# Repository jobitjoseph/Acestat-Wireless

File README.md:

# Acestat-Wireless
Acestat Wireless

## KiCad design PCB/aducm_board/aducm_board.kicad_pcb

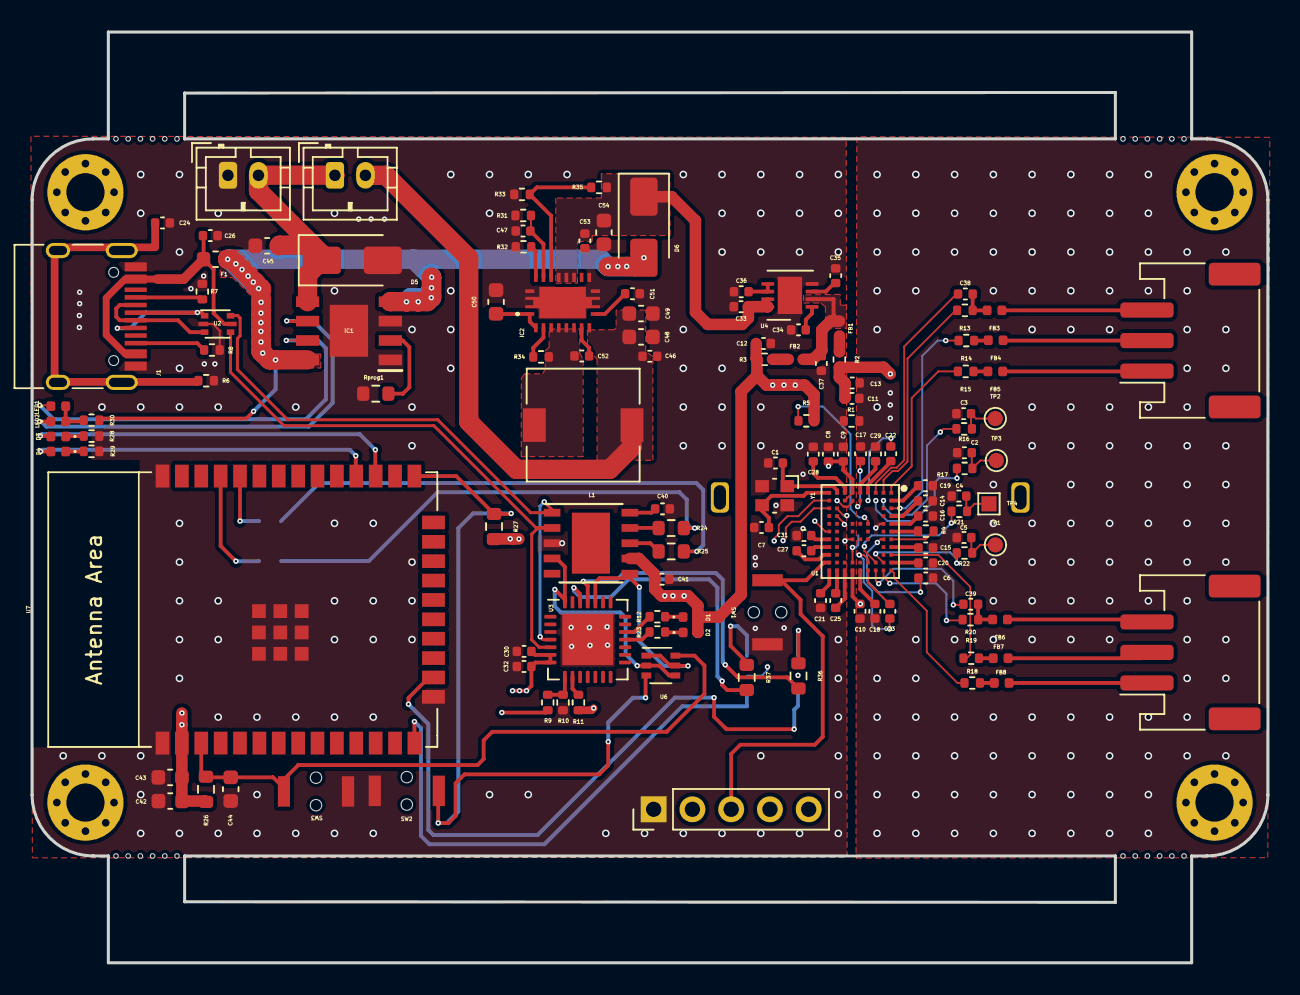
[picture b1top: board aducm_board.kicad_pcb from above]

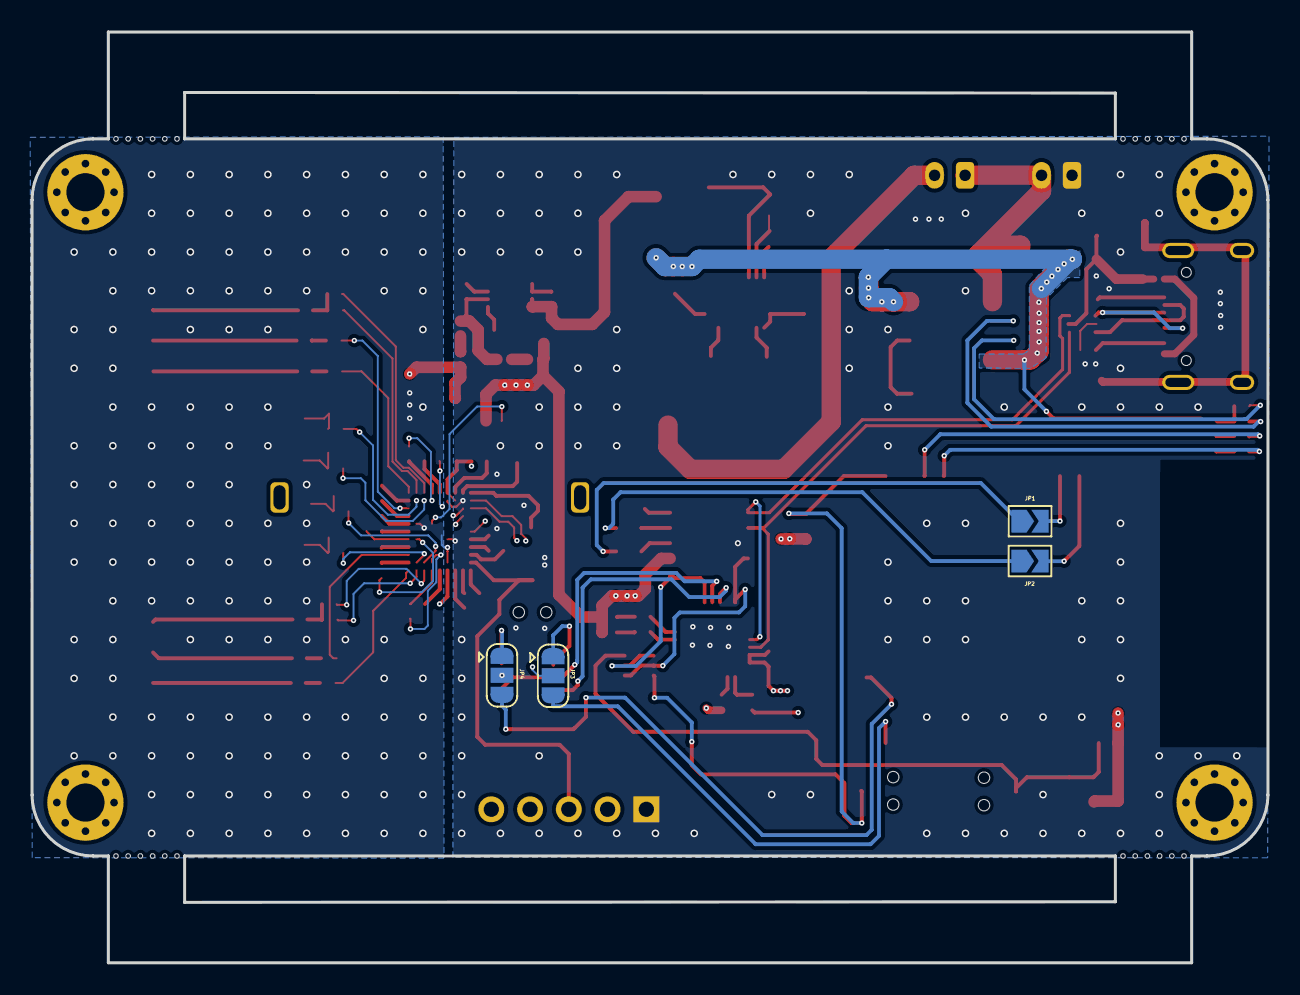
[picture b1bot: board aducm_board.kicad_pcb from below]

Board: 4 copper layers, 81.0 x 61.0 mm, 142 parts (4 on the bottom side), 117 nets.

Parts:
C1, C7: 7pF; C_0402_1005Metric
C2, C3, C4, C5, C8, C9, C10, C11, C12, C19, C20, C22, C25, C26, C27, C32, C38, C39: 0.1uF; C_0402_1005Metric
C6: 220pF; C_0402_1005Metric
C13, C30, C33, C34, C37: 10uF; C_0402_1005Metric
C14, C15, C16, C23: 4.7uF; C_0402_1005Metric
C17, C18, C21, C28, C29, C31: 0.47uF; C_0402_1005Metric
C24: 4.7nF; C_0402_1005Metric
C35, C36: 1uF; C_0402_1005Metric
C40, C46, C52, C53: 0.1uf; C_0402_1005Metric
C41: 0.1UF; C_0402_1005Metric
C42, C48, C49: 10uf; C_0603_1608Metric
C43: 1uf; C_0603_1608Metric
C44: 0.1uf; C_0603_1608Metric
C45: 10uF; C_0603_1608Metric
C47: 470pf; C_0402_1005Metric
C50: 2.2uf; C_0603_1608Metric
C51: 8.2nf; C_0402_1005Metric
C54: 100uf; C_0603_1608Metric
D1, D3, D4: TX; LED_0402_1005Metric
D2: RX; LED_0402_1005Metric
D5, D6: 1N4007; D_SMA
F1: 0.5A; Fuse_0603_1608Metric
FB1, FB2, FB3, FB4, FB5, FB6, FB7, FB8: Ferrite_Bead; L_0402_1005Metric
H1, H2, H3, H4: MountingHole; MountingHole_2.5mm_Pad_Via
IC1: TP4056; SOIC127P600X175-9N
IC2: TPS61088QRHLRQ1
J1: USB_C_Receptacle_USB2.0; USB_C_Receptacle_HRO_TYPE-C-31-M-12
J2, J5: B2B-PH-SM4-TB(LF)(SN); JST_PH_B2B-PH-K_1x02_P2.00mm_Vertical
J3, J4: EC_Sensor_Input_3_Pin; JST_PH_S3B-PH-SM4-TB_1x03-1MP_P2.00mm_Horizontal
J7: JTAG; PinHeader_1x05_P2.54mm_Vertical
JP1, JP2: Jumper_2_Open; SolderJumper-2_P1.3mm_Open_TrianglePad1.0x1.5mm
JP3, JP4: Jumper_3_Open; SolderJumper-3_P1.3mm_Open_RoundedPad1.0x1.5mm
L1: 2.2uH; L_7.3x7.3_H4.5
LED1, LED2: CHG; LED_0402_1005Metric
R1, R13, R14, R15, R16, R17, R18, R19, R20, R21, R22: 0; R_0402_1005Metric
R2, R3: 2.2; R_0402_1005Metric
R4: 200; R_0402_1005Metric
R5: 100k; R_0402_1005Metric
R6: 1M; R_0402_1005Metric
R7, R8: 5K1; R_0402_1005Metric
R9: 22.1K; R_0402_1005Metric
R10: 47.5K; R_0402_1005Metric
R11, R12, R23, R28, R29: 1K; R_0402_1005Metric
R24, R25, R36, R37: 1K; R_0603_1608Metric
R26, R27: 10k; R_0603_1608Metric
R30: 1.3K; R_0402_1005Metric
R31: 23.7k; R_0402_1005Metric
R32: 105k; R_0402_1005Metric
R33: 69.8k; R_0402_1005Metric
R34: 267k; R_0402_1005Metric
R35: 220k; R_0402_1005Metric
Rprog1: 1.2K; R_0603_1608Metric
SW1: SW_Push; Tactile 3x4x2mm TS-A010
SW2, SW3: TS-1088R-02526; Tactile 3x4x2mm TS-A010
TP1, TP2, TP3: TestPoint; TestPoint_Pad_D1.0mm
TP4: TestPoint; TestPoint_Pad_1.0x1.0mm
U1: aducm_355; aducm355
U2: USBLC6-2P6; SOT-666
U3: CP2102N-A01-GQFN28; QFN-28-1EP_5x5mm_P0.5mm_EP3.35x3.35mm
U4: ADM7154; LFCSP_8Lead_CP_8_21
U5: ch340k; ESSOP-10_3.9x4.9mm_P1.00mm
U6: 2N27002DW; SOT-363_SC-70-6
U7: ESP32-WROOM-E; ESP32-WROOM-32E
U8: EMI Shield
Y1: 32MHz; Crystal_SMD_Abracon_ABM10-4Pin_2.5x2.0mm

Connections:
3.3V: C37.1, FB1.2, FB2.2, U4.2 (VOUT)
5VUSB: C26.2, F1.2, J1.A4 (VBUS), J1.A9 (VBUS), J1.B4 (VBUS), J1.B9 (VBUS), U2.5 (VBUS)
+5V: C33.1, C53.1, C54.1, D6.1 (K), IC2.14 (VOUT_1), IC2.15 (VOUT_2), IC2.16 (VOUT_3), R35.1, U4.7 (EN), U4.8 (VIN)
+BATT: C45.1, D5.1 (K), IC1.5 (BAT), J2.2, J5.1
/AIN3: C6.1, U1.B7 (AIN3/BUF_VREF1V8)
/CAP_POT0: C38.2, U1.C1 (CAP_POT0)
/CAP_POT1: C39.2, U1.C11 (CAP_POT1)
/CE0: C38.1, FB3.2, R13.1
/CE0x: R13.2, U1.B1 (CE0)
/CE1: C39.1, FB6.2, R20.1
/CE1x: R20.2, U1.B11 (CE1)
/D+: U2.6 (I/O1), U3.4 (D+), U5.1 (D+)
/D-: U2.4 (I/O2), U3.5 (D-), U5.2 (D-)
/DTR: U3.28 (~DTR), U5.4 (DTR), U6.2, U6.4
/EN: C44.1, R26.1, SW3.1 (A), U6.6, U7.3 (EN/CHIP_PU)
/IO0: R27.1, SW2.1 (A), U6.3, U7.25 (GPIO0/BOOT/ADC2_CH1)
/IO12: JP3.3 (B), U7.14 (MTDI/GPIO12/ADC2_CH5)
/IO13: JP4.3 (B), U7.16 (MTCK/GPIO13/ADC2_CH4)
/P1.1: R5.1, U1.D5 (BM/P1.1)
/RE0: FB5.2, R15.1
/RE0x: R15.2, U1.A1 (RE0)
/RE1: FB8.2, R18.2
/RE1x: R18.1, U1.A11 (RE1)
/RTS: U3.24 (~RTS), U5.6 (RTS), U6.1, U6.5
/RX: JP2.1 (A), JP4.1 (A), R24.1, R36.1
/RX1: JP2.2 (B), U7.35 (U0TXD/GPIO1)
/SWCLK: J7.5, U1.H3 (SWCLK)
/SWDIO: J7.4, U1.H4 (SWDIO)
/TX: JP1.1 (A), JP3.1 (A), R25.1, R37.1
/TX1: JP1.2 (B), U7.34 (U0RXD/GPIO3)
/UART_SIN: JP3.2 (C), U1.J2 (P0.11/UART_SIN)
/UART_SOUT: JP4.2 (C), U1.J3 (P0.10/UART_SOUT)
/VBIAS0: C2.1, R17.1, TP3.1
/VBIAS0x: R17.2, U1.C2 (VBIAS0)
/VBIAS1: C4.1, R21.1, TP4.1
/VBIAS1x: R21.2, U1.C10 (VBIAS1)
/VZERO0: C3.1, R16.1, TP2.1
/VZERO0x: R16.2, U1.B2 (VZero0)
/VZERO1: C5.1, R22.1, TP1.1
/VZERO1x: R22.2, U1.B10 (VZero1)
/WE0: FB4.2, R14.1
/WE0x: R14.2, U1.A3 (SE0)
/WE1: FB7.2, R19.2
/WE1x: R19.1, U1.A9 (SE1)
/XTALI: C1.1, U1.H1 (XTALI), Y1.1
/XTALO: C7.1, U1.J1 (XTALO), Y1.3
/~RESET: J7.3, SW1.1, U1.J10 (~RESET)
/~RST: R11.2, U3.9 (~RSTb)
AGND: C2.2, C3.2, C4.2, C5.2, C6.2, C10.2, C11.2, C13.2, C14.2, C15.1, C16.2, C17.2, C18.2, C19.1, C20.1, C29.2, R1.2, U1.B5 (AGND_REF), U1.F10 (AGND)
AVDD: C10.1, C11.1, C13.1, R2.2, U1.F11 (AVDD)
DGND: C1.2, C7.2, C8.2, C9.2, C12.2, C21.2, C24.2, C26.1, C28.2, C30.2, C31.2, C32.2, C33.2, C34.2, C35.2, C36.2, C37.2, C40.1, C41.1, C42.2, C43.2, C44.2, C45.2, C46.2, C47.2, C48.2, C49.2, C50.2, C51.2, C53.2, C54.2, D5.2 (A), IC1.1 (TEMP), IC1.3 (GND), IC1.9 (EP), IC2.11 (NC_1), IC2.12 (NC_2), IC2.20 (AGND), IC2.21 (EP_1), IC2.22 (EP_2), IC2.23 (EP_3), IC2.24 (EP_4), IC2.25 (EP_5), IC2.26 (EP_6), IC2.27 (EP_7), J1.A1 (GND), J1.A12 (GND), J1.B1 (GND), J1.B12 (GND), J2.1, J7.1, R1.1, R6.2, R7.2, R8.2, R10.2, R28.1, R29.1, R31.1, R32.1, R33.2, Rprog1.2, SW1.2, SW2.2 (B), SW3.2 (B), U1.F2 (DGND_AD), U1.F7 (DGND), U1.H2 (AGND_DD), U2.2 (GND), U3.3 (GND), U3.29 (GND), U4.4 (GND), U4.9 (PAD), U5.3 (GND), U7.1 (GND), U7.15 (GND), U7.38 (GND), U7.39 (GND_THERMAL), Y1.2, Y1.4
DVDD: C8.1, C9.1, C12.1, C30.1, C32.1, C41.2, C42.1, C43.1, D1.2 (A), D2.2 (A), J7.2, R3.2, R5.2, R11.1, R26.2, R27.2, U1.F1 (DVDD_AD), U1.G2 (AVDD_DD), U1.J6 (DVDD), U3.6 (VDD), U3.7 (REGIN), U5.7 (VCC), U7.2 (3V3)
unnamed: D1.1 (K), R12.2
unnamed: D2.1 (K), R23.2
unnamed: D3.2 (A), U7.27 (GPIO16)
unnamed: D3.1 (K), R28.2
unnamed: D4.2 (A), U7.28 (GPIO17)
unnamed: D4.1 (K), R29.2
unnamed: FB1.1, R2.1
unnamed: FB2.1, R3.1
unnamed: IC1.2 (PROG), Rprog1.1
unnamed: IC1.7 (~CHRG), LED1.1 (K)
unnamed: IC1.6 (~STDBY), LED2.1 (K)
unnamed: C52.1, IC2.8 (BOOT)
unnamed: C47.1, IC2.18 (COMP), R31.2
unnamed: C50.1, IC2.1 (VCC), IC2.2 (EN)
unnamed: IC2.17 (FB), R33.1, R35.2
unnamed: IC2.3 (FSW), R34.2
unnamed: IC2.19 (ILIM), R32.2
unnamed: C51.1, IC2.10 (SS)
unnamed: C52.2, IC2.4 (SW_1), IC2.5 (SW_2), IC2.6 (SW_3), IC2.7 (SW_4), L1.2, R34.1
unnamed: J1.A5 (CC1), R7.1
unnamed: J1.B5 (CC2), R8.1
unnamed: J1.A6 (D+), J1.B6 (D+), U2.1 (I/O1)
unnamed: J1.A7 (D-), J1.B7 (D-), U2.3 (I/O2)
unnamed: C24.1, J1.S1 (SHIELD), R6.1
unnamed: FB5.1, J3.1
unnamed: FB4.1, J3.2
unnamed: FB3.1, J3.3
unnamed: FB8.1, J4.1
unnamed: FB7.1, J4.2
unnamed: FB6.1, J4.3
unnamed: LED1.2 (A), LED2.2 (A), R30.2
unnamed: C18.1, U1.E11 (ADCVBIAS_CAP)
unnamed: C14.1, U1.A4 (AIN4_LPF0)
unnamed: C15.2, U1.A8 (AIN7_LPF1)
unnamed: C29.1, U1.E1 (AVDD_REG)
unnamed: C19.2, U1.A2 (DE0)
unnamed: C20.2, U1.A10 (DE1)
unnamed: C31.1, U1.J7 (DVDD_REG)
unnamed: C28.1, U1.G1 (DVDD_REG_AD)
unnamed: C22.1, U1.D1 (RC0_0)
unnamed: C22.2, U1.D2 (RC0_1)
unnamed: C23.1, U1.D11 (RC1_0)
unnamed: C23.2, U1.D10 (RC1_1)
unnamed: R4.1, U1.A7 (RCAL0)
unnamed: R4.2, U1.A6 (RCAL1)
unnamed: C27.1, U1.J8 (VDCDC_CAP1N)
unnamed: C25.1, U1.H11 (VDCDC_CAP2N)
unnamed: C25.2, U1.G11 (VDCDC_CAP2P)
unnamed: C21.1, U1.J11 (VDCDC_CAPOUT~)
unnamed: C27.2, U1.J9 (VDCVC_CAP1P)
unnamed: C16.1, U1.A5 (VREF_1.82V)
unnamed: C17.1, U1.E2 (VREF_2.5V)
unnamed: R36.2, U3.25 (RXD)
unnamed: R37.2, U3.26 (TXD)
unnamed: R9.2, R10.1, U3.8 (VBUS)
unnamed: R23.1, U3.18 (~RXT/GPIO.1)
unnamed: R12.1, U3.19 (~TXT/GPIO.0)
unnamed: C35.1, U4.3 (BYP)
unnamed: C36.1, U4.5 (REF_SENSE), U4.6 (REF)
unnamed: C34.1, U4.1 (VREG)
unnamed: R24.2, U5.9 (RXD)
unnamed: R25.2, U5.8 (TXD)
unnamed: C40.2, U5.10 (V3)
VBUS: D6.2 (A), F1.1, IC1.4 (VCC), IC1.8 (CE), R9.1, R30.1
VDD: C46.1, C48.1, C49.1, IC2.9 (VIN), J5.2, L1.1

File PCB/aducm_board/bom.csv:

Designator,Footprint,Quantity,Value,LCSC Part #
"C1, C7",402,2,7pF,C2991471
"C10, C11, C12, C19, C2, C20, C22, C25, C26, C27, C3, C32, C38, C39, C4, C40, C41, C46, C5, C52, C53, C8, C9",402,23,0.1uF,C307331
"C13, C30, C33, C34, C37",402,5,10uF,C15525
"C14, C15, C16, C23",402,4,4.7uF,C23733
"C17, C18, C21, C28, C29, C31",402,6,0.47uF,C47339
C24,402,1,4.7nF,C1538
"C35, C36",402,2,1uF,C52923
"C42, C45, C48, C49",603,4,10uf,C96446
C43,603,1,1uf,C15849
C44,603,1,0.1uf,C14663
C47,402,1,470pf,C1537
C50,603,1,2.2uf,C23630
C51,402,1,8.2nf,C307436
C54,603,1,22uf,C59461
C6,402,1,220pF,C1530
"D1, D3, LED1",402,3,LED 0402,C364556
"D2, D4, LED2",402,3,LED 0402,C130724
"D5, D6",D_SMA,2,ss34,C8678
F1,603,1,0.5A,C207014
"FB1, FB2",402,2,Ferrite_Bead,C88970
"FB3, FB4, FB5, FB6, FB7, FB8",402,6,Ferrite_Bead,C193387
IC1,SOIC127P600X175-9N,1,TP4056,C16581
IC2,TPS61088QRHLRQ1,1,TPS61088QRHLRQ1,C87357
J1,USB_C_Receptacle_HRO_TYPE-C-31-M-12,1,USB_C_Receptacle_USB2.0,C2765186
"J3, J4",JST_PH_S3B-PH-SM4-TB_1x03-1MP_P2.00mm_Horizontal,2,EC_Sensor_Input_3_Pin,C265101
L1,L_7.3x7.3_H4.5,1,2.2uH,C2847481
"R1, R13, R14, R15, R16, R17, R18, R19, R20, R21, R22",402,11,0,C163804
R10,402,1,47.5K,C25896
"R11, R12, R23, R28, R29",402,5,1K,C11702
"R2, R3",402,2,2.2,C25101
"R24, R25, R36, R37",603,4,1K,C21190
"R26, R27",603,2,10k,C25804
R30,402,1,1.2K,C25768
R31,402,1,23.7k,C327362
R32,402,1,105k,C3015669
R33,402,1,69.8k,C26985
R34,402,1,267k,C159057
R35,402,1,220k,C25767
R4,402,1,200,C25087
R5,402,1,100k,C25741
R6,402,1,1M,C26083
"R7, R8",402,2,5K1,C25905
R9,402,1,22.1K,C25768
Rprog1,603,1,1.2K,C25768
SW1,Tactile 3x4x2mm TS-A010,1,SW_Push,C455280
"SW2, SW3",Tactile 3x4x2mm TS-A010,2,TS-1088R-02526 ,C455280
U1,aducm355,1,aducm_355,C660220
U2,SOT-666,1,USBLC6-2P6,C15999
U3,QFN-28-1EP_5x5mm_P0.5mm_EP3.35x3.35mm,1,CP2102N-A01-GQFN28,C6568
U4,LFCSP_8Lead_CP_8_21,1,ADM7154,C209353
U6,SOT-363_SC-70-6,1,2N7002DW,C83571
Y1,Crystal_SMD_Abracon_ABM10-4Pin_2.5x2.0mm,1,32MHz,C337674
